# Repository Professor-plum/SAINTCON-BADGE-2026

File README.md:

# SAINTCON-BADGE-2026
Electronic badge for SAINTCON2026

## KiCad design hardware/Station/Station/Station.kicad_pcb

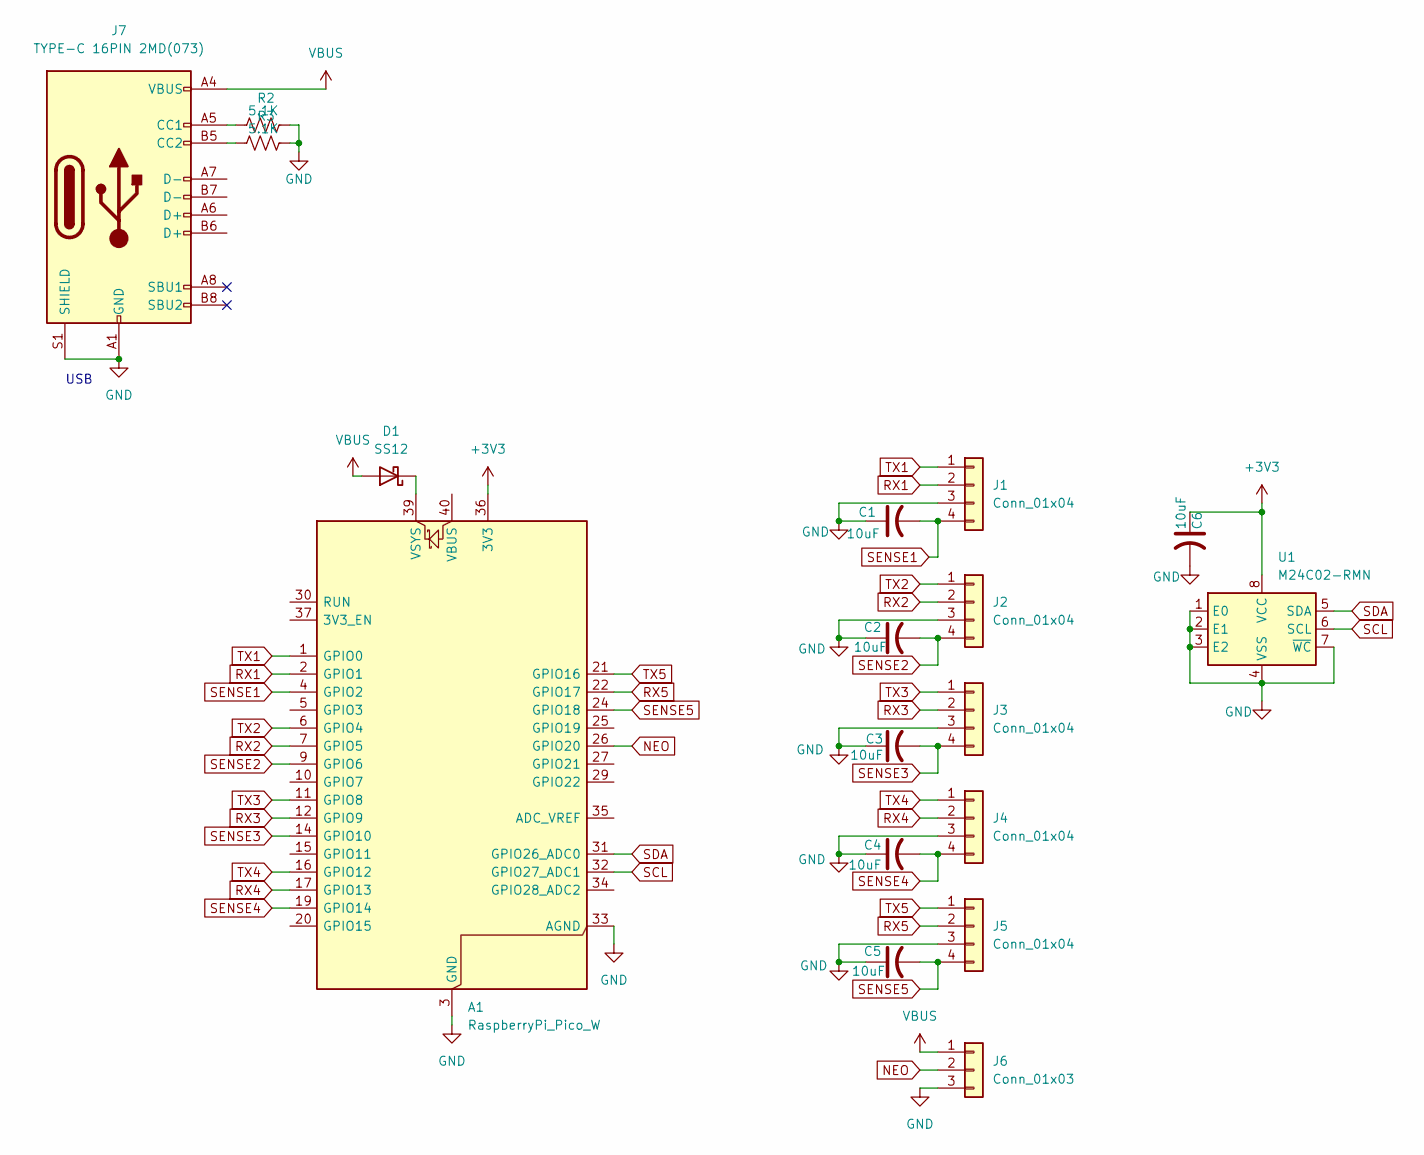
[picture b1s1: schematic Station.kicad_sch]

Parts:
A1: RaspberryPi_Pico_W; RaspberryPi_Pico_W_SMD_HandSolder
C1, C2, C3, C4, C5, C6: 10uF; C_0603_1608Metric_Pad1.08x0.95mm_HandSolder
D1: SS12; D_SMA
J1, J2, J3, J4, J5: Conn_01x04; PinHeader_1x04_P2.54mm_Vertical
J6: Conn_01x03; PinHeader_1x03_P2.54mm_Vertical
J7: TYPE-C 16PIN 2MD(073); USB_C_Receptacle_GCT_USB4105-xx-A_16P_TopMnt_Horizontal; LCSC Part C2765186
R2, R3: 5.1K; R_0603_1608Metric; LCSC Part C2907044
U1: M24C02-RMN; SOIC-8_3.9x4.9mm_P1.27mm

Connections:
+3V3: A1.36 (3V3), C6.1, U1.8 (VCC)
GND: A1.3 (GND), A1.8 (GND), A1.13 (GND), A1.18 (GND), A1.23 (GND), A1.28 (GND), A1.33 (AGND), A1.38 (GND), C1.1, C2.1, C3.1, C4.1, C5.1, C6.2, J1.3, J2.3, J3.3, J4.3, J5.3, J6.3, J7.A1 (GND), J7.A12 (GND), J7.B1 (GND), J7.B12 (GND), J7.S1 (SHIELD), R2.2, R3.2, U1.1 (E0), U1.2 (E1), U1.3 (E2), U1.4 (VSS), U1.7 (~WC)
NEO: A1.26 (GPIO20), J6.2
unnamed: A1.39 (VSYS), D1.1 (K)
unnamed: J7.A5 (CC1), R2.1
unnamed: J7.B5 (CC2), R3.1
RX1: A1.2 (GPIO1), J1.2
RX2: A1.7 (GPIO5), J2.2
RX3: A1.12 (GPIO9), J3.2
RX4: A1.17 (GPIO13), J4.2
RX5: A1.22 (GPIO17), J5.2
SCL: A1.32 (GPIO27_ADC1), U1.6 (SCL)
SDA: A1.31 (GPIO26_ADC0), U1.5 (SDA)
SENSE1: A1.4 (GPIO2), C1.2, J1.4
SENSE2: A1.9 (GPIO6), C2.2, J2.4
SENSE3: A1.14 (GPIO10), C3.2, J3.4
SENSE4: A1.19 (GPIO14), C4.2, J4.4
SENSE5: A1.24 (GPIO18), C5.2, J5.4
TX1: A1.1 (GPIO0), J1.1
TX2: A1.6 (GPIO4), J2.1
TX3: A1.11 (GPIO8), J3.1
TX4: A1.16 (GPIO12), J4.1
TX5: A1.21 (GPIO16), J5.1
VBUS: D1.2 (A), J6.1, J7.A4 (VBUS), J7.A9 (VBUS), J7.B4 (VBUS), J7.B9 (VBUS)

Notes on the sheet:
USB

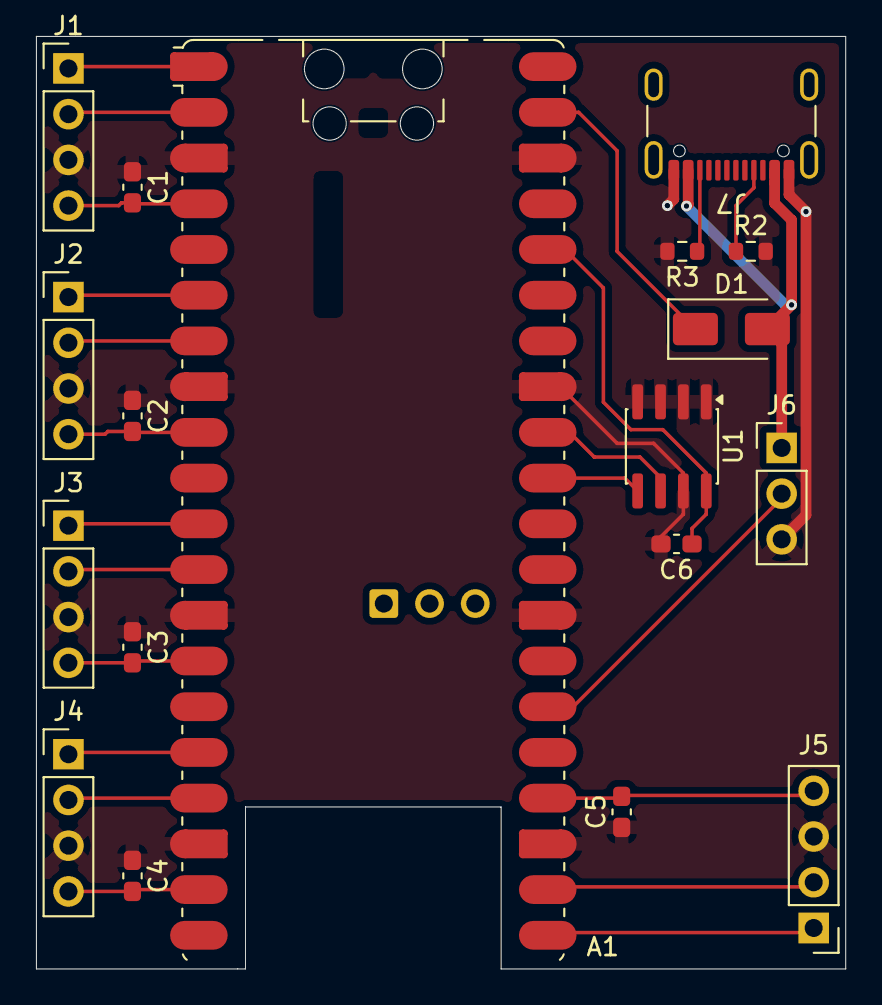
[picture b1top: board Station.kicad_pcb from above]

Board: 2 copper layers, 45.0 x 51.8 mm, 18 parts (0 on the bottom side), 24 nets.

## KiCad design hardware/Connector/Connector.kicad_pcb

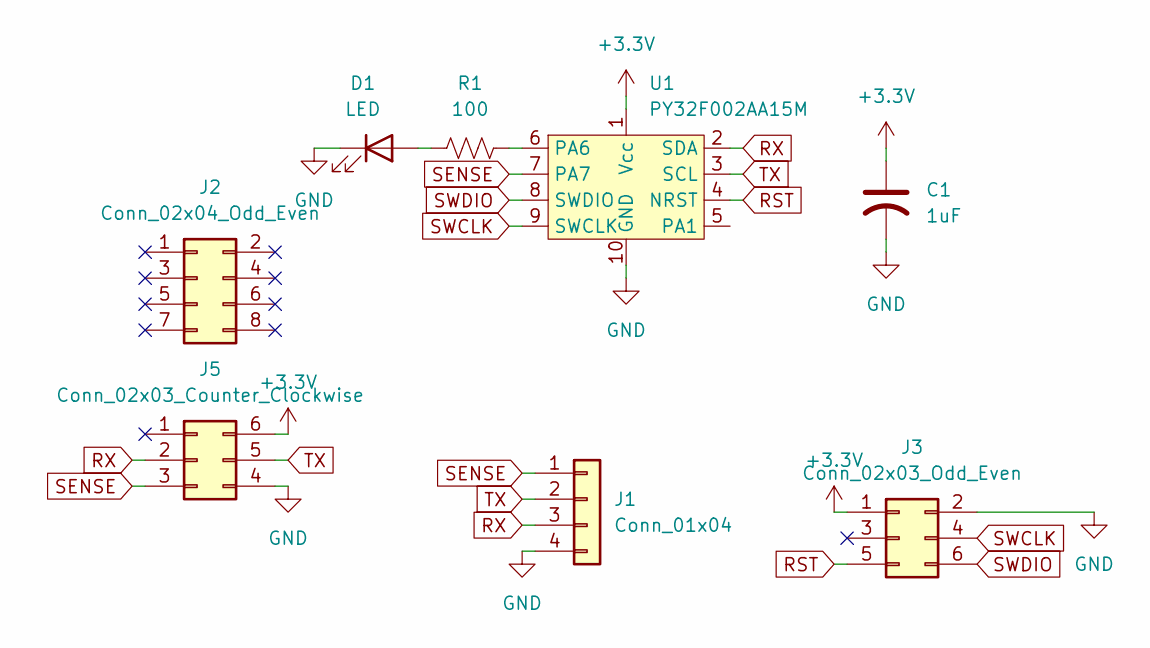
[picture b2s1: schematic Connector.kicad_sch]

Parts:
C1: 1uF; C_0603_1608Metric
D1: LED; LED_0603_1608Metric
J1: Conn_01x04; RJ45-TH_RRCH-52014P4C
J2: Conn_02x04_Odd_Even; CONN-TH_ER08BGFBK
J3: Conn_02x03_Odd_Even; PinHeader_2x03_P1.27mm_Vertical
J5: Conn_02x03_Counter_Clockwise; CONN-TH_6P-P2.54_ER06BGFBK
R1: 100; R_0603_1608Metric
U1: PY32F002AA15M; SSOP-10_3.9x4.9mm_P1.00mm

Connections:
+3.3V: C1.1, J3.1, J5.6, U1.1 (Vcc)
GND: C1.2, D1.1 (K), J1.4, J3.2, J5.4, U1.10 (GND)
unnamed: D1.2 (A), R1.2
unnamed: R1.1, U1.6 (PA6)
RST: J3.5, U1.4 (NRST)
RX: J1.3, J5.2, U1.2 (SDA)
SENSE: J1.1, J5.3, U1.7 (PA7)
SWCLK: J3.4, U1.9 (SWCLK)
SWDIO: J3.6, U1.8 (SWDIO)
TX: J1.2, J5.5, U1.3 (SCL)

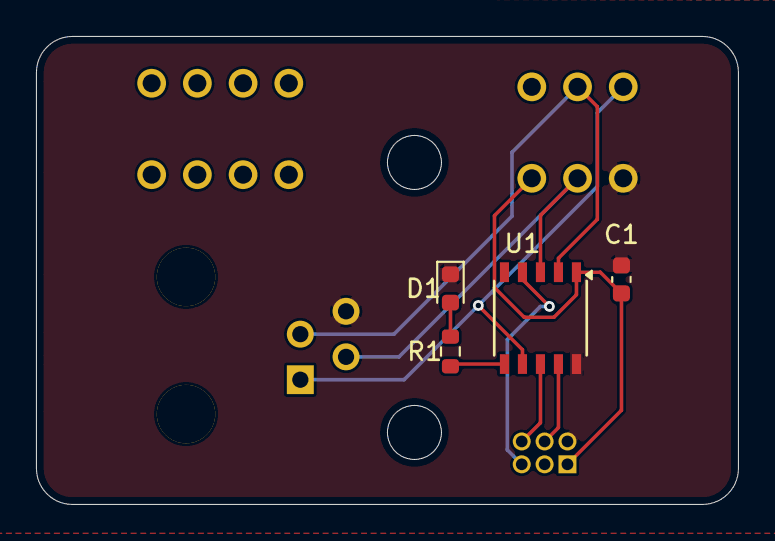
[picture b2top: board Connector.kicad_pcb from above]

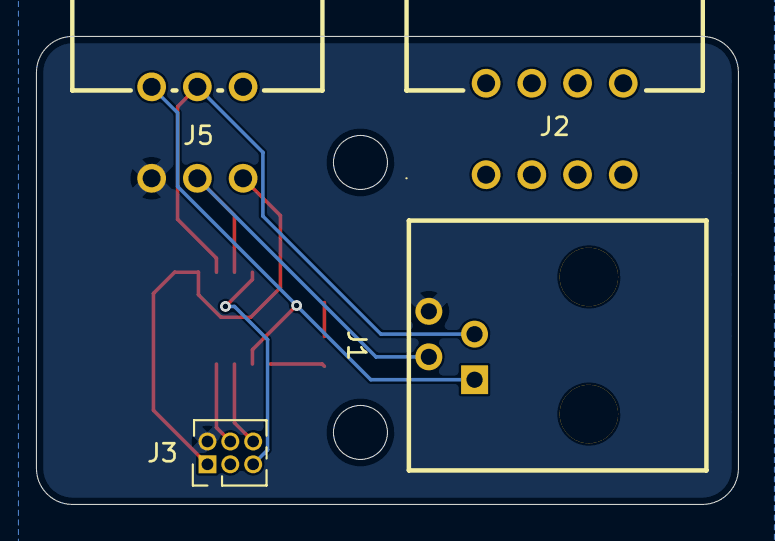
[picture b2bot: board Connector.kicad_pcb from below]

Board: 2 copper layers, 39.0 x 26.0 mm, 8 parts (4 on the bottom side), 10 nets.

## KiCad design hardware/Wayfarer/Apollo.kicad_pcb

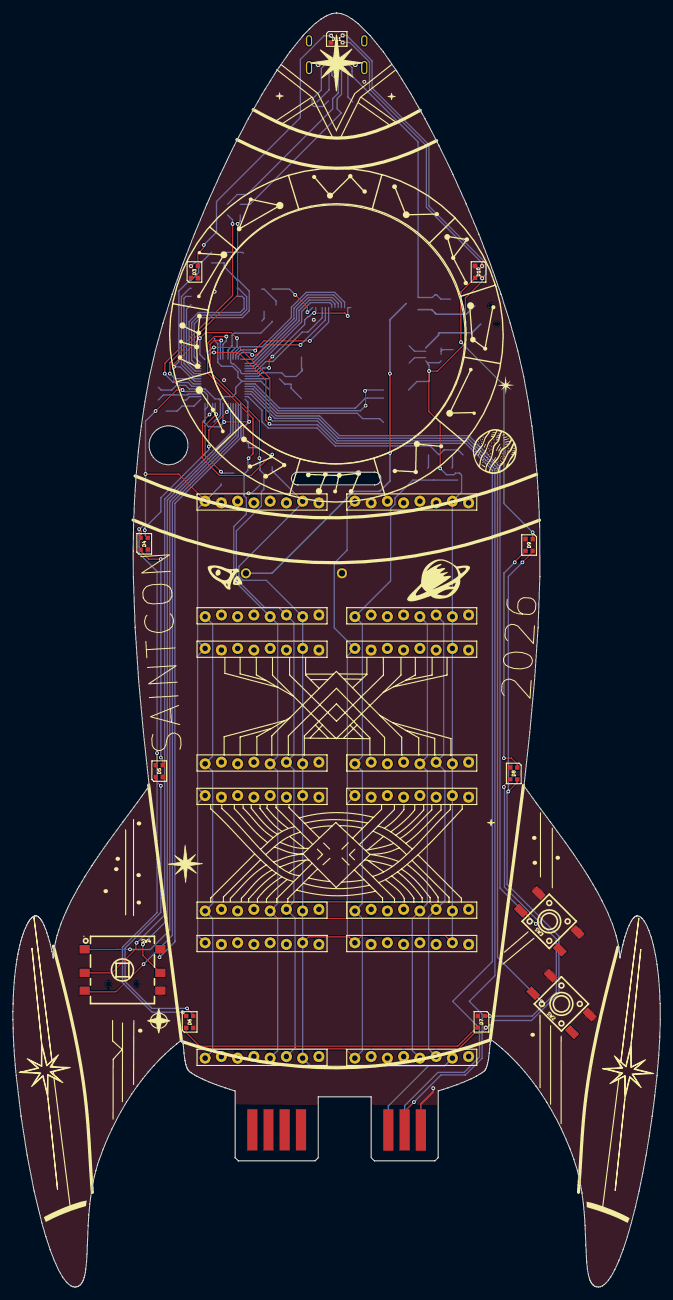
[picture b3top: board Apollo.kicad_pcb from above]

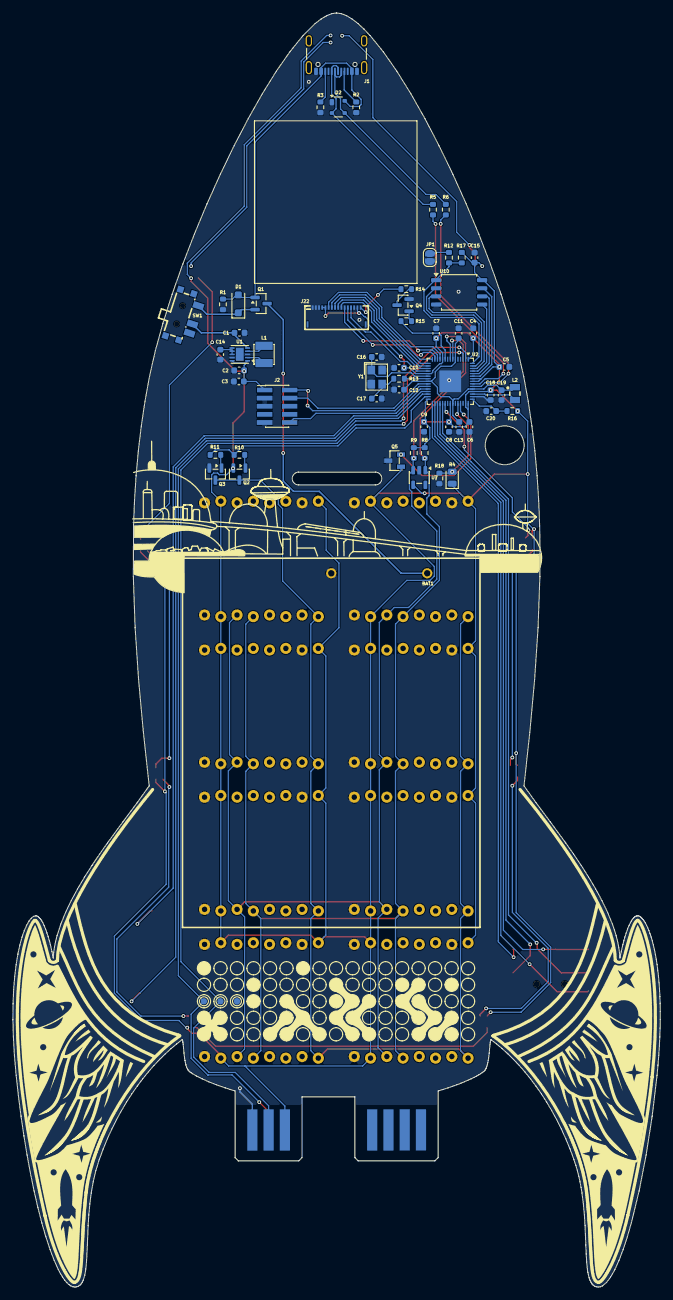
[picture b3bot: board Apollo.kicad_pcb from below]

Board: 2 copper layers, 101.2 x 199.1 mm, 82 parts (60 on the bottom side), 69 nets.

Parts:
BAT1: BH-AA-A1AJ029; BAT-TH_BH-AA-A1AJ029
C1, C13, C18, C19, C20: 4.7uF; C_0603_1608Metric
C2, C3: 10uF; C_0603_1608Metric
C4, C5, C6, C7, C8, C9, C10, C11, C12, C15: 100nF; C_0603_1608Metric
C14: 0.1uF; C_0603_1608Metric
C16, C17: 15pF; C_0603_1608Metric
D1: MBR1020VL; D_SOD-123F
D2: SP0503BAHTG; SOT-143
D3, D4, D5, D6, D7, D8, D9, D10, D11: WS2812C; LED_WS2812B-2020_PLCC4_2.0x2.0mm
J1: TYPE-C 16PIN 2MD(073); USB_C_Receptacle_GCT_USB4105-xx-A_16P_TopMnt_Horizontal
J2: Conn_ARM_JTAG_SWD_10; PinHeader_2x05_P1.27mm_Vertical_SMD
J3: Conn_02x03_Odd_Even; PCB_Edge_6
J4: Conn_02x04_Odd_Even; PCB_Edge_8
J22: Conn_01x16; CONN-SMD_16P-P0.50_5034801600_1
JP1: Jumper_2_Open; SolderJumper-2_P1.3mm_Open_RoundedPad1.0x1.5mm
L1: 1.5uH; IND-SMD_L3.0-W3.0_FNR30XXS
L2: 3.3uH; IND-SMD_L2.0-W1.6_AOTA-B201610S3R3-101-T
Q1: DMP1045U-7; SOT-23
Q2: SS8550; SOT-23
Q3, Q4: SS8050; SOT-23
Q5: SL1254-3; SOT-23-3_L2.9-W1.3-P1.90-LS2.4-BR
R1: 100K; R_0603_1608Metric
R2, R3: 5.1K; R_0603_1608Metric
R4: PT0805; LED_0805_2012Metric
R5, R6, R14: 27; R_0603_1608Metric
R8, R9: 4.7K; R_0603_1608Metric
R10, R11, R12: 10K; R_0603_1608Metric
R13, R15, R18: 1K; R_0603_1608Metric
R16: 33; R_0603_1608Metric
R17: DNP; R_0603_1608Metric
SW1: MK-12C01-G1.5; SW-SMD_DEALON_MK-12C01-G1.5
SW2, SW3: TS-1095PS-A1B2-C3D2; KEY-SMD_4P-L6.0-W6.0-P3.90-LS9.0
SW4: 10*10*9-6P WX; SW-SMD-6P-L10.5-W10.0_C2858290
TP1, TP2, TP3: TestPoint; TestPoint_Pad_D1.0mm
U1: TPS63031DSK; WSON-10-1EP_2.5x2.5mm_P0.5mm_EP1.2x2mm
U2: RP2350A-QFN60; QFN-60-1EP_7x7mm_P0.4mm_EP3.4x3.4mm
U3, U4, U5, U6, U8, U9, U11, U12: SAINTCON-Minibadge; MiniBadge_Slot_Lock
U7: 24CS02; SOT-23-5
U10: PY25Q128HA; SOIC-8_5.3x5.3mm_P1.27mm
Y1: 12Mhz; CRYSTAL-SMD_4P-L3.2-W2.5-BL

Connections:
1HZ_CLK: Q2.3 (C), Q3.3 (C), U3.9 (CLK), U4.9 (CLK), U5.9 (CLK), U6.9 (CLK), U8.9 (CLK), U9.9 (CLK), U11.9 (CLK), U12.9 (CLK)
+1V1: C11.1, C12.1, C13.1, C19.1, L2.2, U2.6 (DVDD), U2.23 (DVDD), U2.39 (DVDD), U2.50 (VREG_FB)
+3.3V: C2.1, C3.1, C4.1, C5.1, C6.1, C7.1, C8.1, C9.1, C10.1, C15.1, C18.1, D3.4 (VDD), D4.4 (VDD), D5.4 (VDD), D6.4 (VDD), D7.4 (VDD), D8.4 (VDD), D9.4 (VDD), D10.4 (VDD), D11.4 (VDD), J2.1 (VTref), J3.2, J22.4, J22.5, J22.15, Q2.2 (E), Q5.1 (VDD), R4.1, R8.2, R9.2, R16.2, R17.1, U1.1 (VOUT), U1.10 (FB), U2.1 (IOVDD), U2.11 (IOVDD), U2.20 (IOVDD), U2.30 (IOVDD), U2.38 (IOVDD), U2.44 (ADC_AVDD), U2.45 (IOVDD), U2.49 (VREG_VIN), U2.53 (USB_OTP_VDD), U2.54 (QSPI_IOVDD), U3.1 (+5V), U3.7 (+3v3), U3.15 (+3v3), U4.1 (+5V), U4.7 (+3v3), U4.15 (+3v3), U5.1 (+5V), U5.7 (+3v3), U5.15 (+3v3), U6.1 (+5V), U6.7 (+3v3), U6.15 (+3v3), U7.4 (VCC), U8.1 (+5V), U8.7 (+3v3), U8.15 (+3v3), U9.1 (+5V), U9.7 (+3v3), U9.15 (+3v3), U10.8 (VCC), U11.1 (+5V), U11.7 (+3v3), U11.15 (+3v3), U12.1 (+5V), U12.7 (+3v3), U12.15 (+3v3)
BTN1: SW2.2, U2.28 (GPIO17)
BTN2: SW3.2, U2.27 (GPIO16)
GND: BAT1.1, C1.2, C2.2, C3.2, C4.2, C5.2, C6.2, C7.2, C8.2, C9.2, C10.2, C11.2, C12.2, C13.2, C14.2, C15.2, C16.2, C17.2, C18.2, C19.2, C20.2, D2.1 (A), D3.2 (VSS), D4.2 (VSS), D5.2 (VSS), D6.2 (VSS), D7.2 (VSS), D8.2 (VSS), D9.2 (VSS), D10.2 (VSS), D11.2 (VSS), J1.A1 (GND), J1.A12 (GND), J1.B1 (GND), J1.B12 (GND), J2.3 (GND), J2.5 (GND), J2.9 (GNDDetect), J3.5, J3.6, J22.1, J22.2, J22.3, J22.14, JP1.1 (A), Q3.2 (E), Q4.2 (E), Q5.3 (GND), R1.1, R2.2, R3.2, R18.1, SW2.3, SW2.4, SW3.3, SW3.4, SW4.4, TP3.1 (1_1), U1.3 (PGND), U1.9 (GND), U1.11 (PGND), U2.47 (VREG_PGND), U2.61 (GND), U3.2 (GND), U3.8 (GND), U3.16 (GND), U4.2 (GND), U4.8 (GND), U4.16 (GND), U5.2 (GND), U5.8 (GND), U5.16 (GND), U6.2 (GND), U6.8 (GND), U6.16 (GND), U7.2 (GND), U8.2 (GND), U8.8 (GND), U8.16 (GND), U9.2 (GND), U9.8 (GND), U9.16 (GND), U10.4 (GND), U11.2 (GND), U11.8 (GND), U11.16 (GND), U12.2 (GND), U12.8 (GND), U12.16 (GND), Y1.2, Y1.4
HALL: Q5.2 (OUT), U2.42 (GPIO28_ADC2)
JOY_B: SW4.6, U2.31 (GPIO19)
JOY_D: SW4.3, U2.32 (GPIO20)
JOY_L: SW4.2, U2.35 (GPIO23)
JOY_R: SW4.5, U2.34 (GPIO22)
JOY_U: SW4.1, U2.33 (GPIO21)
LCD_BL: R15.1, U2.10 (GPIO7)
LCD_BUSY: J22.6, U2.12 (GPIO8)
LCD_CLK: J22.12, U2.14 (GPIO10)
LCD_CS: J22.13, U2.19 (GPIO15)
LCD_IO1: J22.8, U2.16 (GPIO12)
LCD_IO2: J22.9, U2.17 (GPIO13)
LCD_IO3: J22.10, U2.18 (GPIO14)
LCD_MOSI: J22.7, U2.15 (GPIO11)
LCD_RST: J22.11, U2.13 (GPIO9)
LIGHT: R4.2, R18.2, U2.41 (GPIO27_ADC1)
MB_CLK: R10.2, R11.2, U2.29 (GPIO18)
NEO_PIX: D4.3 (DIN), U2.36 (GPIO24)
unnamed: C17.1, R13.1, Y1.3
unnamed: D1.1 (K), Q1.2 (S), SW1.3 (C)
unnamed: D4.1 (DOUT), D5.3 (DIN)
unnamed: D5.1 (DOUT), D6.3 (DIN)
unnamed: D6.1 (DOUT), D7.3 (DIN)
unnamed: D7.1 (DOUT), D8.3 (DIN)
unnamed: D8.1 (DOUT), D9.3 (DIN)
unnamed: D9.1 (DOUT), D10.3 (DIN)
unnamed: D10.1 (DOUT), D11.3 (DIN)
unnamed: D3.3 (DIN), D11.1 (DOUT)
unnamed: J1.A5 (CC1), R2.1
unnamed: J1.B5 (CC2), R3.1
unnamed: J22.16, R14.2
unnamed: JP1.2 (B), R12.1
unnamed: BAT1.2, Q1.3 (D)
unnamed: Q2.1 (B), R10.1
unnamed: Q3.1 (B), R11.1
unnamed: Q4.1 (B), R15.2
unnamed: Q4.3 (C), R14.1
unnamed: C14.1, U1.6 (EN), U1.7 (PS/SYNC), U1.8 (VINA)
unnamed: L1.2, U1.4 (L1)
unnamed: L1.1, U1.2 (L2)
unnamed: R6.2, U2.51 (USB_DM)
unnamed: R5.1, U2.52 (USB_DP)
unnamed: C20.1, R16.1, U2.46 (VREG_AVDD)
unnamed: L2.1, U2.48 (VREG_LX)
unnamed: C16.1, U2.21 (XIN), Y1.1
unnamed: R13.2, U2.22 (XOUT)
unnamed: U2.56 (QSPI_SCLK), U10.6 (CLK)
unnamed: U2.57 (QSPI_SD0), U10.5 (DI/IO_{0})
unnamed: U2.59 (QSPI_SD1), U10.2 (DO/IO_{1})
unnamed: R12.2, R17.2, U2.60 (QSPI_SS), U10.1 (~CS)
unnamed: U2.55 (QSPI_SD3), U10.7 (~HOLD/~RESET/IO_{3})
unnamed: U2.58 (QSPI_SD2), U10.3 (~WP/IO_{2})
RST: J2.10 (~RESET), U2.26 (RUN)
RX: J3.4, TP1.1 (1_1), U2.3 (GPIO1)
SCL: R8.1, U2.8 (GPIO5), U3.13 (SCL), U4.13 (SCL), U5.13 (SCL), U6.13 (SCL), U7.1 (SCL), U8.13 (SCL), U9.13 (SCL), U11.13 (SCL), U12.13 (SCL)
SDA: R9.1, U2.7 (GPIO4), U3.14 (SDA), U4.14 (SDA), U5.14 (SDA), U6.14 (SDA), U7.3 (SDA), U8.14 (SDA), U9.14 (SDA), U11.14 (SDA), U12.14 (SDA)
SWCLK: J2.4 (SWCLK/TCK), U2.24 (SWCLK)
SWDIO: J2.2 (SWDIO/TMS), U2.25 (SWDIO)
TX: J3.3, TP2.1 (1_1), U2.2 (GPIO0)
USB_D+: D2.2 (K), J1.A6 (D+), J1.B6 (D+), R5.2
USB_D-: D2.3 (K), J1.A7 (D-), J1.B7 (D-), R6.1
VBUS: D1.2 (A), D2.4 (K), J1.A4 (VBUS), J1.A9 (VBUS), J1.B4 (VBUS), J1.B9 (VBUS), Q1.1 (G), R1.2
VIN: C1.1, SW1.2 (B), U1.5 (VIN)

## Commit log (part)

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2026-05-07 Add common build artifacts to .gitignore
2026-05-07 Added hardware design files
2026-05-07 Move items out of subdirectory
2026-05-07 Add Orion Trail PoC firmware
2026-05-24 prototype v0.3
2026-05-24 Updated joystick
2026-06-05 accel added
2026-06-05 Restoring Orion trail
2026-06-13 Added achievement screen and minor edits
2026-06-19 Progress on station communications
